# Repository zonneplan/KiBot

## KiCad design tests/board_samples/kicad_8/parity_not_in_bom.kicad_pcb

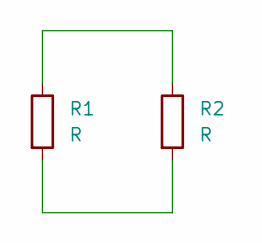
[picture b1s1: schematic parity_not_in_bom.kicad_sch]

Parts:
R1, R2: R; R_0805_2012Metric

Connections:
unnamed: R1.1, R2.1
unnamed: R1.2, R2.2

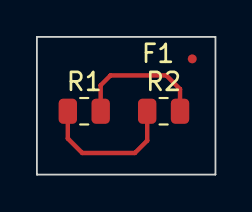
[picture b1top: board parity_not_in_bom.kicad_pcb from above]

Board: 2 copper layers, 9.9 x 7.7 mm, 3 parts (0 on the bottom side), 2 nets.

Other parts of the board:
F1: Fiducial_0.5mm_Mask1.5mm

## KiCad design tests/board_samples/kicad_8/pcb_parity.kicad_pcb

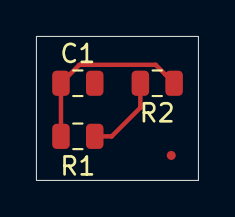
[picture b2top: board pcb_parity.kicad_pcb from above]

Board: 2 copper layers, 9.0 x 8.0 mm, 4 parts (0 on the bottom side), 2 nets.

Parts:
C1: 1uF; C_0805_2012Metric
F1: Fiducial_0.5mm_Mask1.5mm
R1: 100; R_0805_2012Metric
R2: 200; R_0805_2012Metric

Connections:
unnamed: C1.1, R1.2, R2.1
VCC: R1.1, R2.2

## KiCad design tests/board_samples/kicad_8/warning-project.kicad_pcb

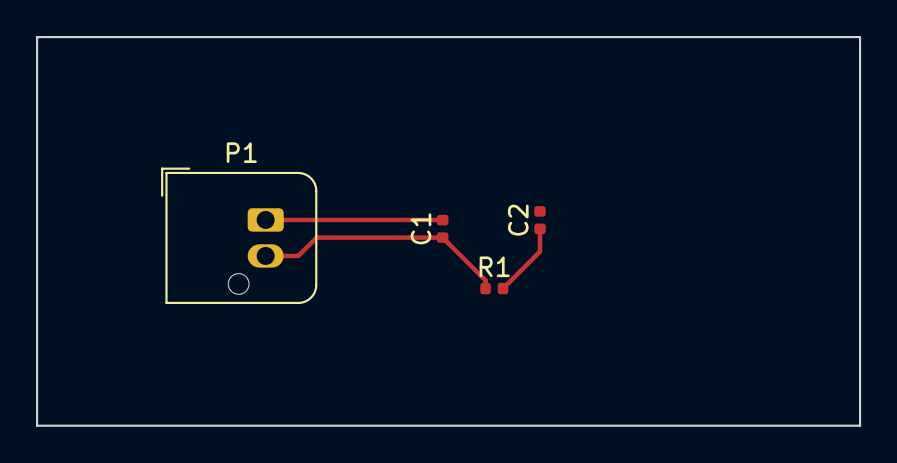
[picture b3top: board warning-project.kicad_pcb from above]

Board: 2 copper layers, 45.7 x 21.6 mm, 4 parts (0 on the bottom side), 3 nets.

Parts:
C1, C2: C; C_0402_1005Metric
P1: CONN_01X02; JST_JWPF_B02B-JWPF-SK-R_1x02_P2.00mm_Vertical
R1: R; R_0402_1005Metric

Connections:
GND: C1.2, C2.2, P1.1
unnamed: C2.1, R1.2
VCC: C1.1, P1.2, R1.1
